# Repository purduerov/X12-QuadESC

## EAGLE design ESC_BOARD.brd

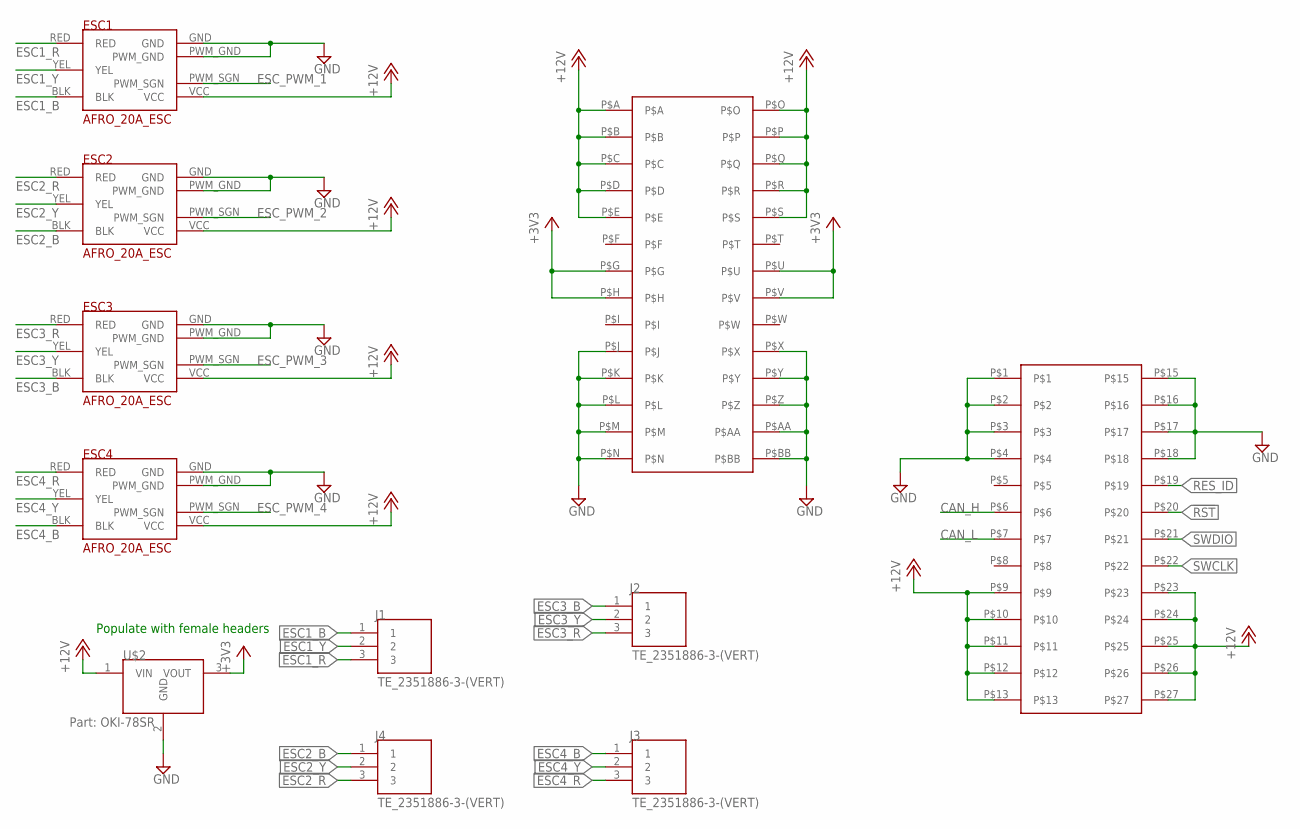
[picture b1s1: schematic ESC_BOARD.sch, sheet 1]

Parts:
ESC1, ESC2, ESC3, ESC4: AFRO_20A_ESC
J1, J2, J3, J4: TE_2351886-3-(VERT)
U$2: MURATA-DC-DC
U$6: ESC2BACKPLANE; ESC2BACKPLANE_WHOLE

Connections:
!RST: U$6.P$20; also elsewhere on the board
+3V3: U$2.3 (VOUT), U$6.P$G, U$6.P$H, U$6.P$U, U$6.P$V; also elsewhere on the board
+12V: ESC1.VCC, ESC2.VCC, ESC3.VCC, ESC4.VCC, U$2.1 (VIN), U$6.P$9, U$6.P$10, U$6.P$11, U$6.P$12, U$6.P$13, U$6.P$23, U$6.P$24, U$6.P$25, U$6.P$26, U$6.P$27, U$6.P$A, U$6.P$B, U$6.P$C, U$6.P$D, U$6.P$E, U$6.P$O, U$6.P$P, U$6.P$Q, U$6.P$R, U$6.P$S
CAN_H: U$6.P$6; also elsewhere on the board
CAN_L: U$6.P$7; also elsewhere on the board
ESC1_B: ESC1.BLK, J1.1
ESC1_R: ESC1.RED, J1.3
ESC1_Y: ESC1.YEL, J1.2
ESC2_B: ESC2.BLK, J4.1
ESC2_R: ESC2.RED, J4.3
ESC2_Y: ESC2.YEL, J4.2
ESC3_B: ESC3.BLK, J2.1
ESC3_R: ESC3.RED, J2.3
ESC3_Y: ESC3.YEL, J2.2
ESC4_B: ESC4.BLK, J3.1
ESC4_R: ESC4.RED, J3.3
ESC4_Y: ESC4.YEL, J3.2
ESC_PWM_1: ESC1.PWM_SGN; also elsewhere on the board
ESC_PWM_2: ESC2.PWM_SGN; also elsewhere on the board
ESC_PWM_3: ESC3.PWM_SGN; also elsewhere on the board
ESC_PWM_4: ESC4.PWM_SGN; also elsewhere on the board
GND: ESC1.GND, ESC1.PWM_GND, ESC2.GND, ESC2.PWM_GND, ESC3.GND, ESC3.PWM_GND, ESC4.GND, ESC4.PWM_GND, U$2.2 (GND), U$6.P$1, U$6.P$2, U$6.P$3, U$6.P$4, U$6.P$15, U$6.P$16, U$6.P$17, U$6.P$18, U$6.P$AA, U$6.P$BB, U$6.P$J, U$6.P$K, U$6.P$L, U$6.P$M, U$6.P$N, U$6.P$X, U$6.P$Y, U$6.P$Z; also elsewhere on the board
RES_ID: U$6.P$19; also elsewhere on the board
SWCLK: U$6.P$22; also elsewhere on the board
SWDIO: U$6.P$21; also elsewhere on the board

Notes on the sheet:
Populate with female headers

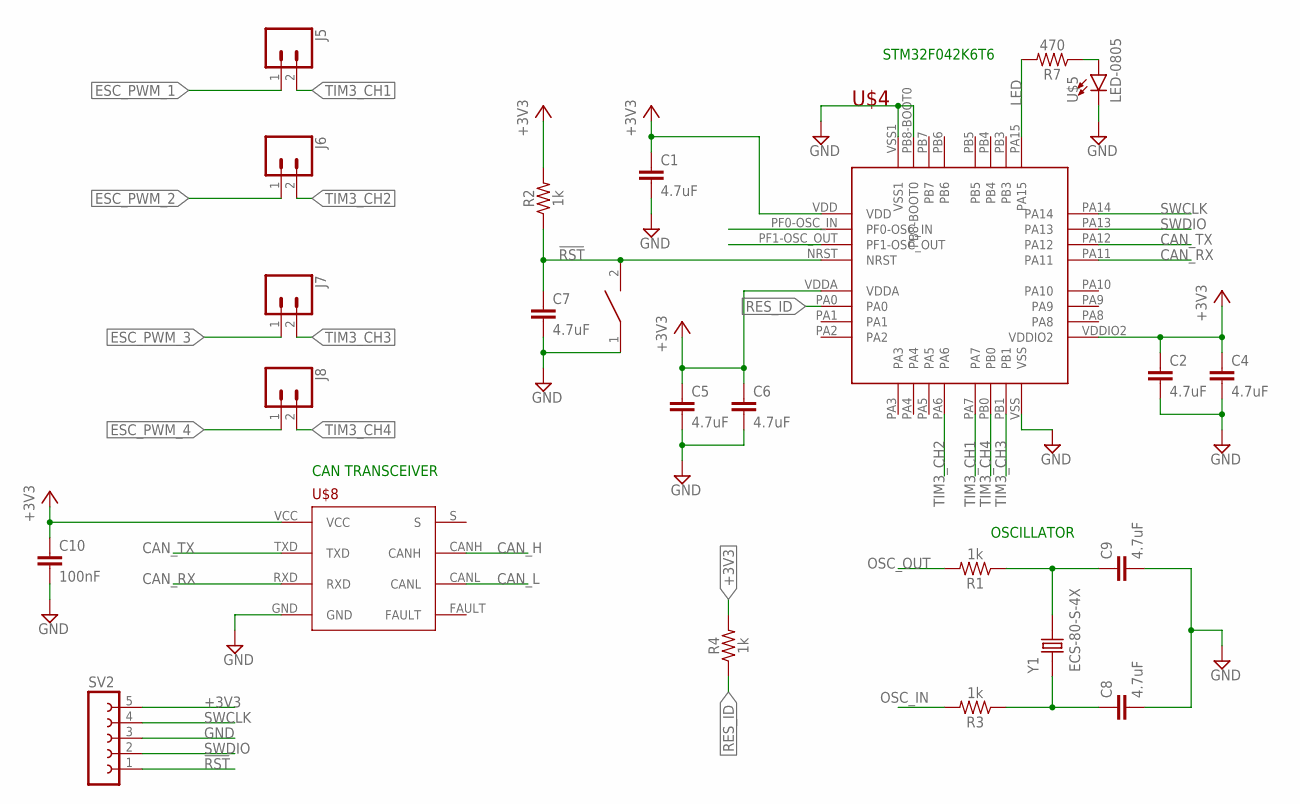
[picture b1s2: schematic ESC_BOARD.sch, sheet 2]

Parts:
C1, C2, C4, C5, C6, C7, C8, C9: 4.7uF; 0603
C10: 100nF; 0603
J5, J6, J7, J8: CONN_02; 1X02
R1, R2, R3, R4: 1k; 0603
R7: 470; 0603
SV2: FE05-1
U$3: DISCRETECOMPONENTS_SWITCH; DISCRETECOMPONENTS_SW_2512
U$4: STM32F042K6T6
U$5: LED-0805; 0805
U$8: TCAN337D
Y1: ECS-80-S-4X; XTAL_ECS-80-S-4X

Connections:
!RST: C7.1, R2.1, SV2.1, U$3.2, U$4.NRST; also elsewhere on the board
+3V3: C1.1, C2.1, C4.1, C5.1, C6.1, C10.1, R2.2, R4.2, SV2.5, U$4.VDD, U$4.VDDA, U$4.VDDIO2, U$8.VCC; also elsewhere on the board
CAN_H: U$8.CANH; also elsewhere on the board
CAN_L: U$8.CANL; also elsewhere on the board
CAN_RX: U$4.PA11, U$8.RXD
CAN_TX: U$4.PA12, U$8.TXD
ESC_PWM_1: J5.1; also elsewhere on the board
ESC_PWM_2: J6.1; also elsewhere on the board
ESC_PWM_3: J7.1; also elsewhere on the board
ESC_PWM_4: J8.1; also elsewhere on the board
GND: C1.2, C2.2, C4.2, C5.2, C6.2, C7.2, C8.2, C9.2, C10.2, SV2.3, U$3.1, U$4.PB8-BOOT0, U$4.VSS, U$4.VSS1, U$5.C, U$8.GND; also elsewhere on the board
LED: R7.2, U$4.PA15
unnamed: C9.1, R1.1, Y1.2
unnamed: C8.1, R3.1, Y1.1
unnamed: R7.1, U$5.A
OSC_IN: R3.2, U$4.PF0-OSC_IN
OSC_OUT: R1.2, U$4.PF1-OSC_OUT
RES_ID: R4.1, U$4.PA0; also elsewhere on the board
SWCLK: SV2.4, U$4.PA14; also elsewhere on the board
SWDIO: SV2.2, U$4.PA13; also elsewhere on the board
TIM3_CH1: J5.2, U$4.PA7
TIM3_CH2: J6.2, U$4.PA6
TIM3_CH3: J7.2, U$4.PB1
TIM3_CH4: J8.2, U$4.PB0

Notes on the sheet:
CAN TRANSCEIVER
OSCILLATOR
STM32F042K6T6

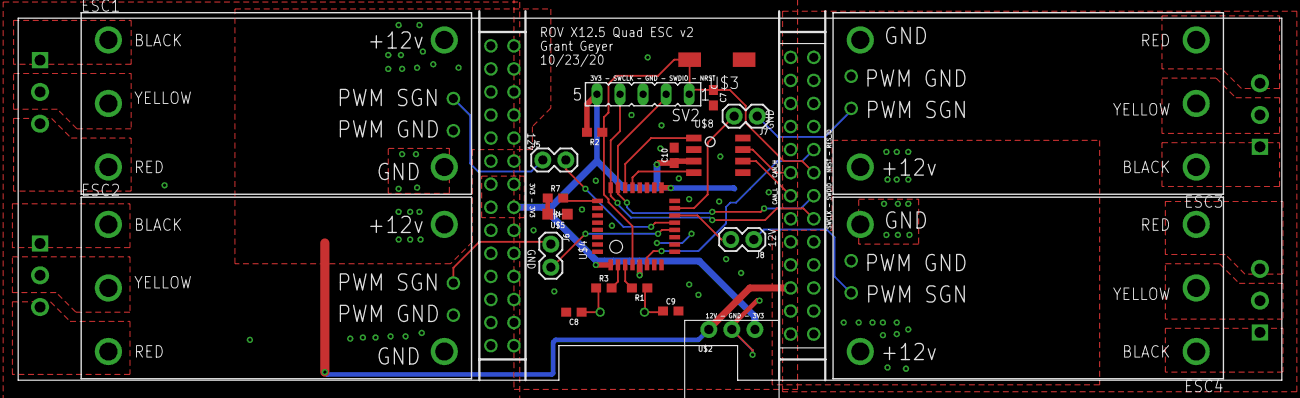
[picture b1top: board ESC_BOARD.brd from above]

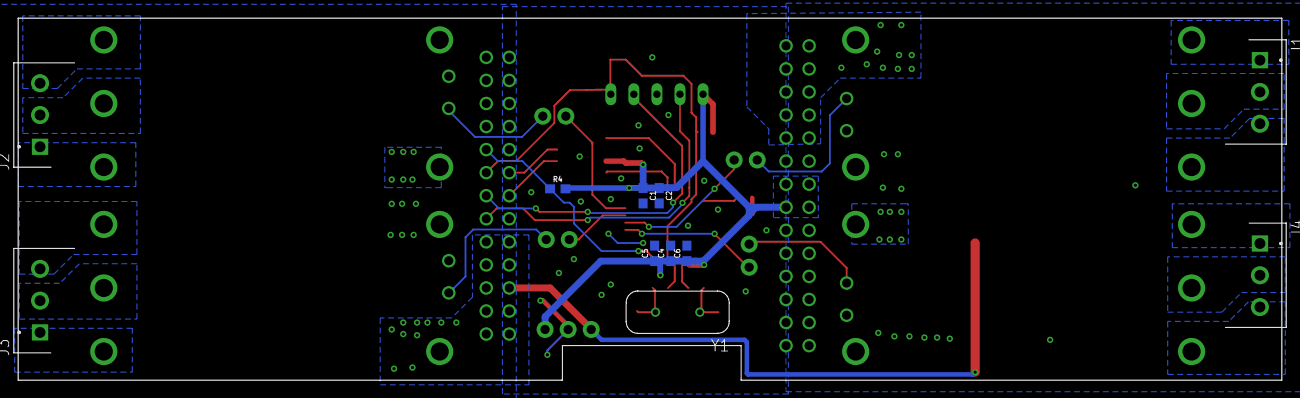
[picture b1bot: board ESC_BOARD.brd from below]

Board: 2 copper layers, 139.2 x 39.9 mm, 34 parts (11 on the bottom side), 37 nets.

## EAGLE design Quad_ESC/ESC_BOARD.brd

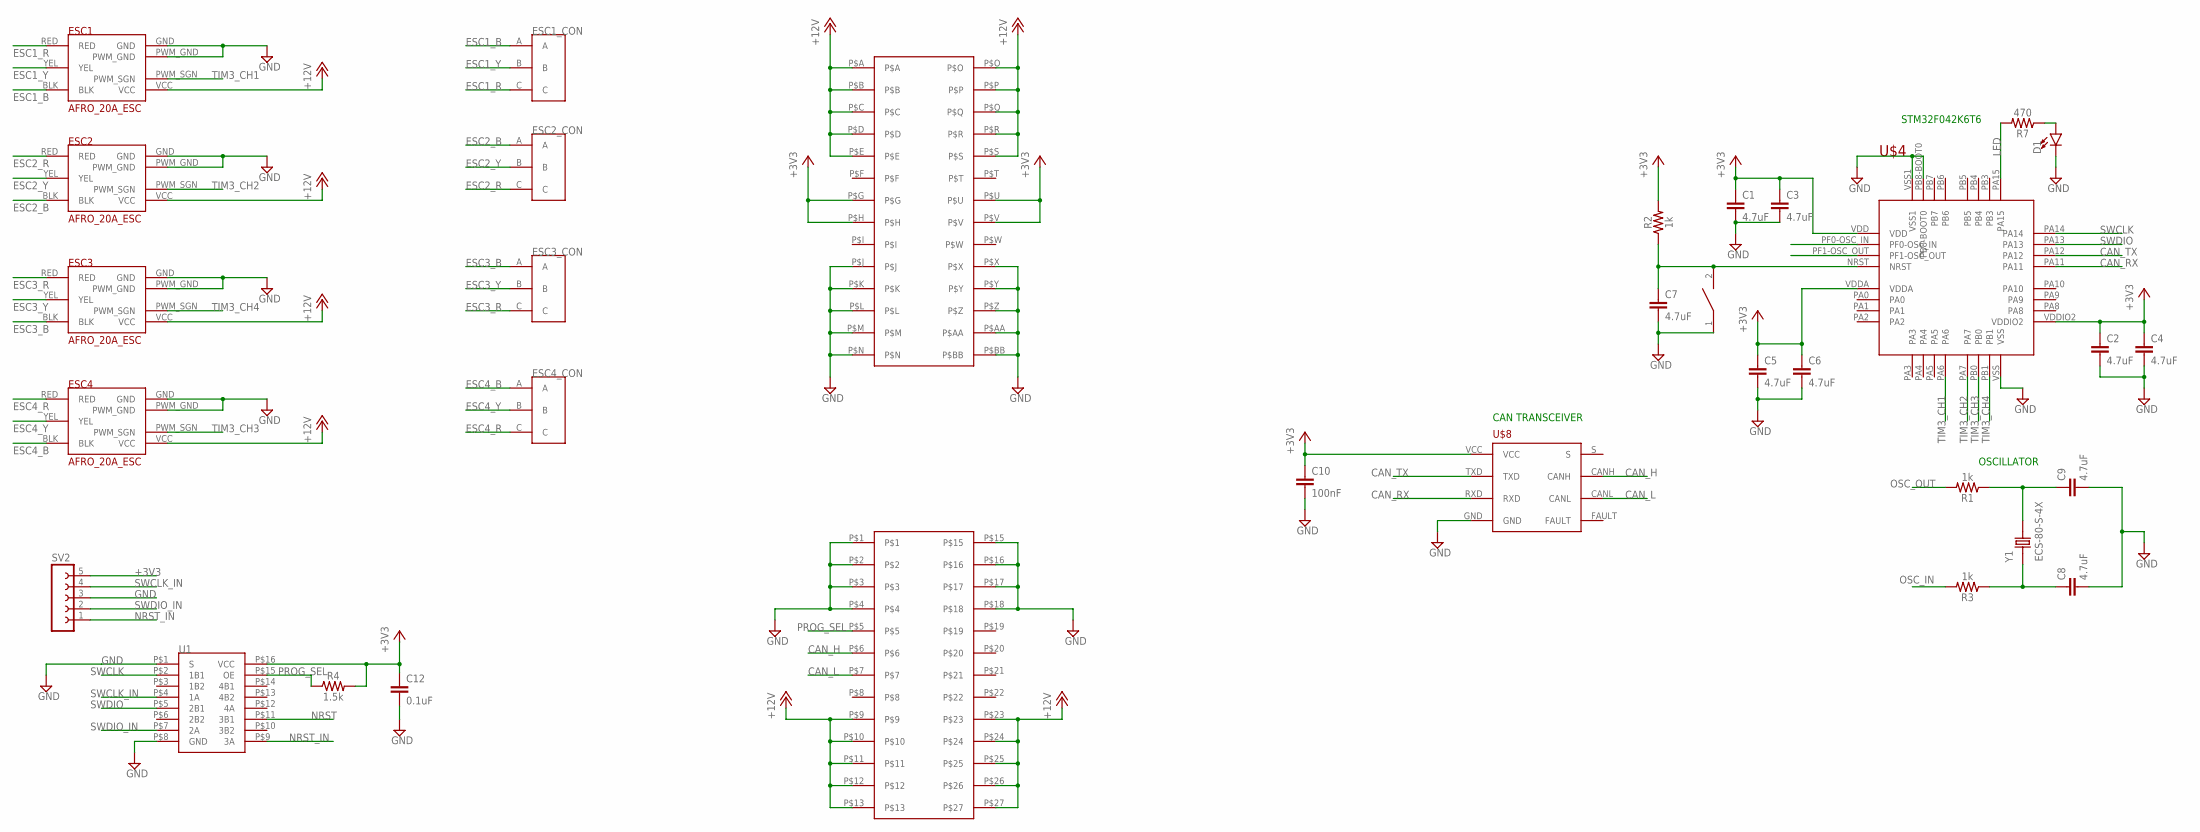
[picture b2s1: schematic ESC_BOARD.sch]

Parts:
C1, C2, C3, C4, C5, C6, C7, C8, C9: 4.7uF; 0603
C10: 100nF; 0603
C12: 0.1uF; 0603
D1: LED0603; LED-0603
ESC1, ESC2, ESC3, ESC4: AFRO_20A_ESC
ESC1_CON, ESC2_CON, ESC3_CON, ESC4_CON: 3PINCONNECTOR
R1, R2, R3: 1k; 0603
R4: 1.5k; 0603
R7: 470; 0603
RESET: SWITCH; SW_2512
SV2: FE05-1
U1: SN74CBTLV3257PWR
U$1: ESC2BACKPLANE; ESC2BACKPLANE_WHOLE
U$4: STM32F042K6T6
U$8: TCAN337D
Y1: ECS-80-S-4X; XTAL_ECS-80-S-4X

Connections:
+3V3: C1.1, C2.1, C3.1, C4.1, C5.1, C6.1, C10.1, C12.1, R2.2, R4.2, SV2.5, U1.P$16 (VCC), U$1.P$G, U$1.P$H, U$1.P$U, U$1.P$V, U$4.VDD, U$4.VDDA, U$4.VDDIO2, U$8.VCC
+12V: ESC1.VCC, ESC2.VCC, ESC3.VCC, ESC4.VCC, U$1.P$9, U$1.P$10, U$1.P$11, U$1.P$12, U$1.P$13, U$1.P$23, U$1.P$24, U$1.P$25, U$1.P$26, U$1.P$27, U$1.P$A, U$1.P$B, U$1.P$C, U$1.P$D, U$1.P$E, U$1.P$O, U$1.P$P, U$1.P$Q, U$1.P$R, U$1.P$S
CAN_H: U$1.P$6, U$8.CANH
CAN_L: U$1.P$7, U$8.CANL
CAN_RX: U$4.PA11, U$8.RXD
CAN_TX: U$4.PA12, U$8.TXD
ESC1_B: ESC1.BLK, ESC1_CON.A
ESC1_R: ESC1.RED, ESC1_CON.C
ESC1_Y: ESC1.YEL, ESC1_CON.B
ESC2_B: ESC2.BLK, ESC2_CON.A
ESC2_R: ESC2.RED, ESC2_CON.C
ESC2_Y: ESC2.YEL, ESC2_CON.B
ESC3_B: ESC3.BLK, ESC3_CON.A
ESC3_R: ESC3.RED, ESC3_CON.C
ESC3_Y: ESC3.YEL, ESC3_CON.B
ESC4_B: ESC4.BLK, ESC4_CON.A
ESC4_R: ESC4.RED, ESC4_CON.C
ESC4_Y: ESC4.YEL, ESC4_CON.B
GND: C1.2, C2.2, C3.2, C4.2, C5.2, C6.2, C7.2, C8.2, C9.2, C10.2, C12.2, D1.C, ESC1.GND, ESC1.PWM_GND, ESC2.GND, ESC2.PWM_GND, ESC3.GND, ESC3.PWM_GND, ESC4.GND, ESC4.PWM_GND, RESET.1, SV2.3, U1.P$1 (S), U1.P$8 (GND), U$1.P$1, U$1.P$2, U$1.P$3, U$1.P$4, U$1.P$15, U$1.P$16, U$1.P$17, U$1.P$18, U$1.P$AA, U$1.P$BB, U$1.P$J, U$1.P$K, U$1.P$L, U$1.P$M, U$1.P$N, U$1.P$X, U$1.P$Y, U$1.P$Z, U$4.PB8-BOOT0, U$4.VSS, U$4.VSS1, U$8.GND
LED: R7.2, U$4.PA15
unnamed: C9.1, R1.1, Y1.2
unnamed: C8.1, R3.1, Y1.1
unnamed: D1.A, R7.1
NRST: C7.1, R2.1, RESET.2, U1.P$11 (3B1), U$4.NRST
NRST_IN: SV2.1, U1.P$9 (3A)
OSC_IN: R3.2, U$4.PF0-OSC_IN
OSC_OUT: R1.2, U$4.PF1-OSC_OUT
PROG_SEL: R4.1, U1.P$15 (OE), U$1.P$5
SWCLK: U1.P$2 (1B1), U$4.PA14
SWCLK_IN: SV2.4, U1.P$4 (1A)
SWDIO: U1.P$5 (2B1), U$4.PA13
SWDIO_IN: SV2.2, U1.P$7 (2A)
TIM3_CH1: ESC1.PWM_SGN, U$4.PA6
TIM3_CH2: ESC2.PWM_SGN, U$4.PA7
TIM3_CH3: ESC4.PWM_SGN, U$4.PB0
TIM3_CH4: ESC3.PWM_SGN, U$4.PB1

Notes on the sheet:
CAN TRANSCEIVER
OSCILLATOR
STM32F042K6T6

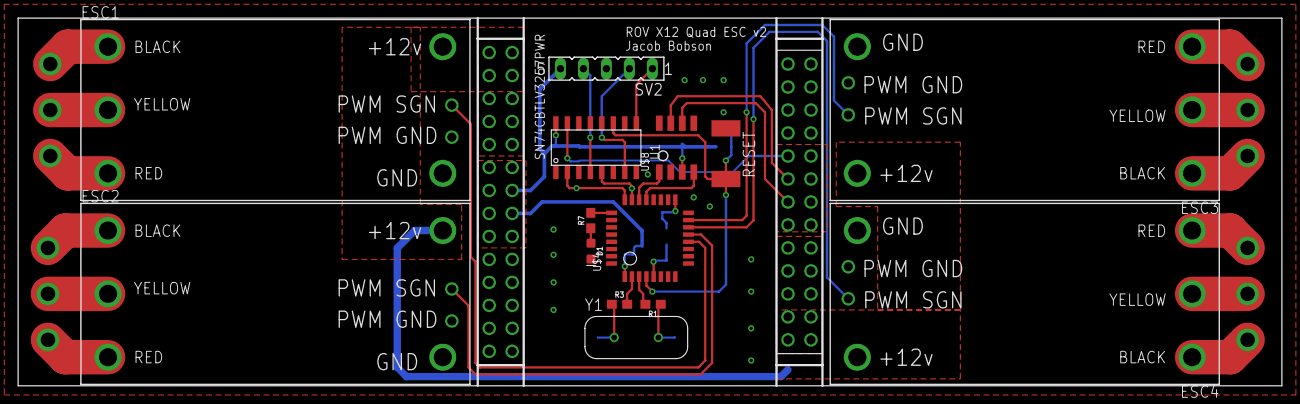
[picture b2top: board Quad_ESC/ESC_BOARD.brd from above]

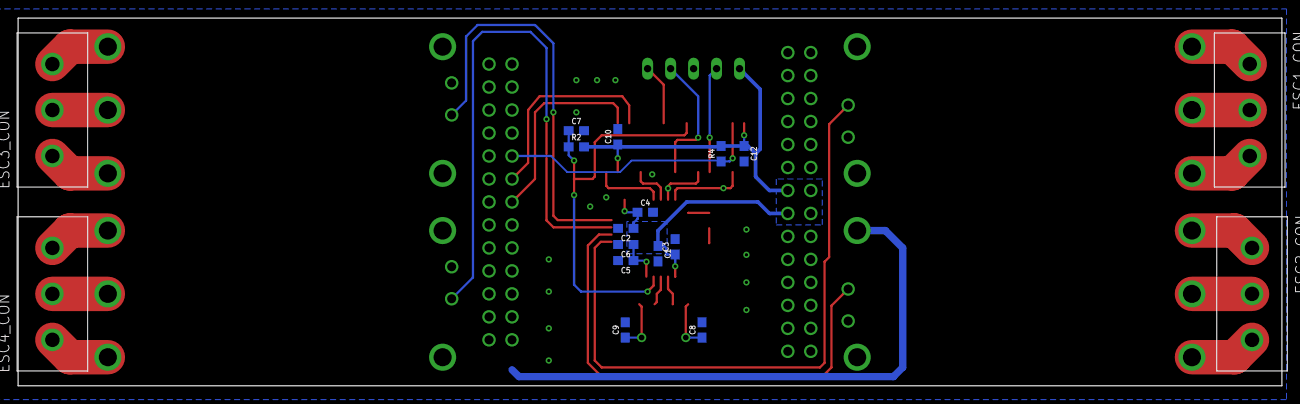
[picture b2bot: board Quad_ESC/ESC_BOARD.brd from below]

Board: 2 copper layers, 139.7 x 40.6 mm, 32 parts (17 on the bottom side), 36 nets.

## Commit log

2019-11-05 Added Test Board
2019-11-06 IDK what i changed
2019-12-30 Labeling
2020-01-07 Moved Label
2020-02-09 added gitignore
2020-03-06 removed back up files
2020-03-06 fixed mux and manufacturing errors
2020-09-04 CAD for ESC board
2020-09-10 cad for connectors to backplane
2020-09-21 fix routings undone by connector switch for cad
2020-09-25 began work on lumenier
2020-09-25 resistor ID added and changed SWD connections
2020-10-23 placed most components
2020-10-23 routed for rev2
2020-10-23 connector CAD and a few touchups
2020-10-24 added pins for programing ESCs
2020-10-26 Silkscreen graphic and order files

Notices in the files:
parts and their libraries:
SparkFun-Capacitors: Licensing: Creative Commons ShareAlike 4.0 International - https://creativecommons.org/licenses/by-sa/4.0
